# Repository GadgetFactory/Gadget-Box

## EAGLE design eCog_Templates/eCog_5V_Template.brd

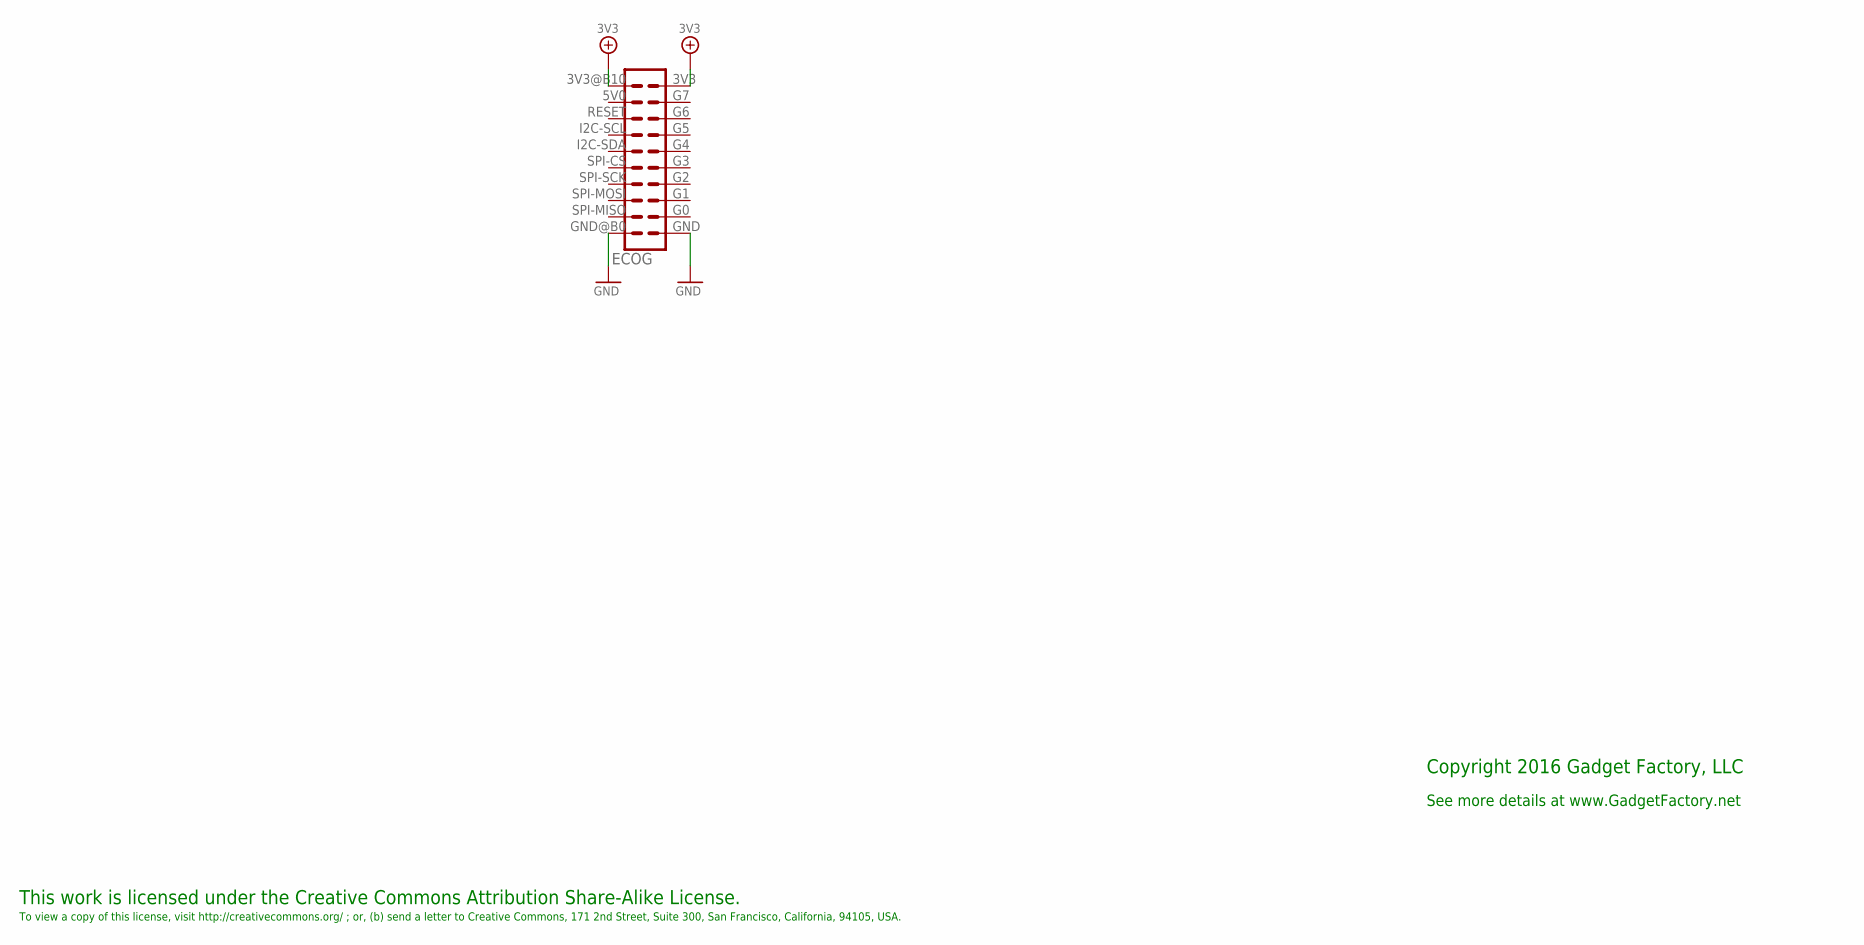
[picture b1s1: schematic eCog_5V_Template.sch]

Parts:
ECOG: ECOG_DUALTHROUGHHOLE; ECOG_DUAL_TH

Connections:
3V3: ECOG.3V3, ECOG.3V3@B10 (3V3)
GND: ECOG.GND, ECOG.GND@B0 (GND)

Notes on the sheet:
This work is licensed under the Creative Commons Attribution Share-Alike License.
To view a copy of this license, visit http://creativecommons.org/ ; or, (b) send a letter to Creative Commons, 171 2nd Street, Suite 300, San Francisco, California, 94105, USA.
Copyright 2016 Gadget Factory, LLC
See more details at www.GadgetFactory.net

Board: 2 copper layers, 11 parts (0 on the bottom side), 2 nets, no tracks yet.

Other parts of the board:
U$1: GADGETBOX_TEXT
U$2, U$3, U$4: LEGEND_DIO
U$5, U$6: LEGEND_PWM
U$7, U$8, U$9: LEGEND_ANALOG
U$10: OSHW_FILLX350_NOTEXT
